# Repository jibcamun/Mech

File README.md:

<h1 align="center">Mech</h1>
<p align="center">A numpad for the elderly</p>

## Purpose
### What is this?
A numpad, consisting numbers from 1 to 9.
### What does this do?
Help people easily access numbers on a keyboard.
### Why does this exists? _(Motivation to build this)_
I have seen old people who use computers only as a calculator and find it hard to type numbers because its stacked at the top and they are more used to the typical calculator layout. _(my grandparents)_

## Features
1. Uses Arduino Pro Micro.
2. Uses MX Switches (1.00u) and Cherry MX Keycaps for a better feel and feedback while pressing a key.  
3. Made it easy to connect and use with a USB connection, thus making it more accessible for the elderly.
4. Simple UX, again making it easily usable for the elderly.
5. All keycaps are angled forward making it easy for "finger typing".

## Schematics

## PCB

## Case

## Zine

## Build Guide
### Step 1
Solder all components to the PCB as indicated by the schematic diagrams.
### Step 2
Take the soldered PCB and place it in an appropriate orientation on the 3D printed component named "Bottom", in accordance with the position of the screw holes.
### Step 3
Place the 3D printed component named "Top" on the assembled setup and press them together _(like a sandwich)_.

## Firmware Flashing
### Step 1
Connect the Pro Micro to your computer using the USB cable.
### Step 2
Install QMK WSYS (if on windows). Enter `qmk flash -kb mech -km default` in the terminal window, to flash the firmware.

## Links 
1. [Bill of Materials (BOM)](https://github.com/jibcamun/Mech/blob/main/Materials/BOM.csv)
2. [PCB Design](https://github.com/jibcamun/Mech/blob/main/PCB%20Design)
3. [3D Case Design](https://cad.onshape.com/documents/927574eef36e39d9a3de9231/w/e5b95da04439b4f215ef18f1/e/b08572cbae5c0041dba6a6c8?renderMode=0&uiState=69ea2cd7de772b1d4ea52e7f)
4. [CAD Export Files](https://github.com/jibcamun/Mech/blob/main/3D%20Models)
5. [3D Export of Design](https://github.com/jibcamun/Mech/blob/main/3D%20Models/mech.step)

## Links for Bill of Materials (Available in BOM)
1. PCBWay: https://www.pcbway.com/
2. ROBU.IN: https://robu.in/product/pro-micro-5v-16m-mini-leonardo-micro-controller-development-board-for-arduino
3. MECKEYS: https://meckeys.com/shop/accessories/keyboard-accessories/key-switches/gateron-mechanical-switch/?attribute_pa_gateron-key-switches=ks-9a10b060nn-x14 
4. Dexterous Manufacturing Labs Pvt Ltd: https://storefront.iamrapid.com/
5. ELECTRONICS COMP: https://www.electronicscomp.com/1n4148-diode

## Attributions 
1. Cherry MX Switches: [row 1 1u blank keycap for cherry mx style switches](https://www.thingiverse.com/thing:5616342) by [LazarosVarvatis](https://www.thingiverse.com/LazarosVarvatis/designs) is licensed under the [Creative Commons - Attribution - Non-Commercial - Share Alike](https://creativecommons.org/licenses/by-nc-sa/4.0/) license. License: [CC BY-NC-SA 4.0](https://creativecommons.org/licenses/by-nc-sa/4.0/)
2. Footprints: [scottokeebs](https://github.com/joe-scotto/scottokeebs)

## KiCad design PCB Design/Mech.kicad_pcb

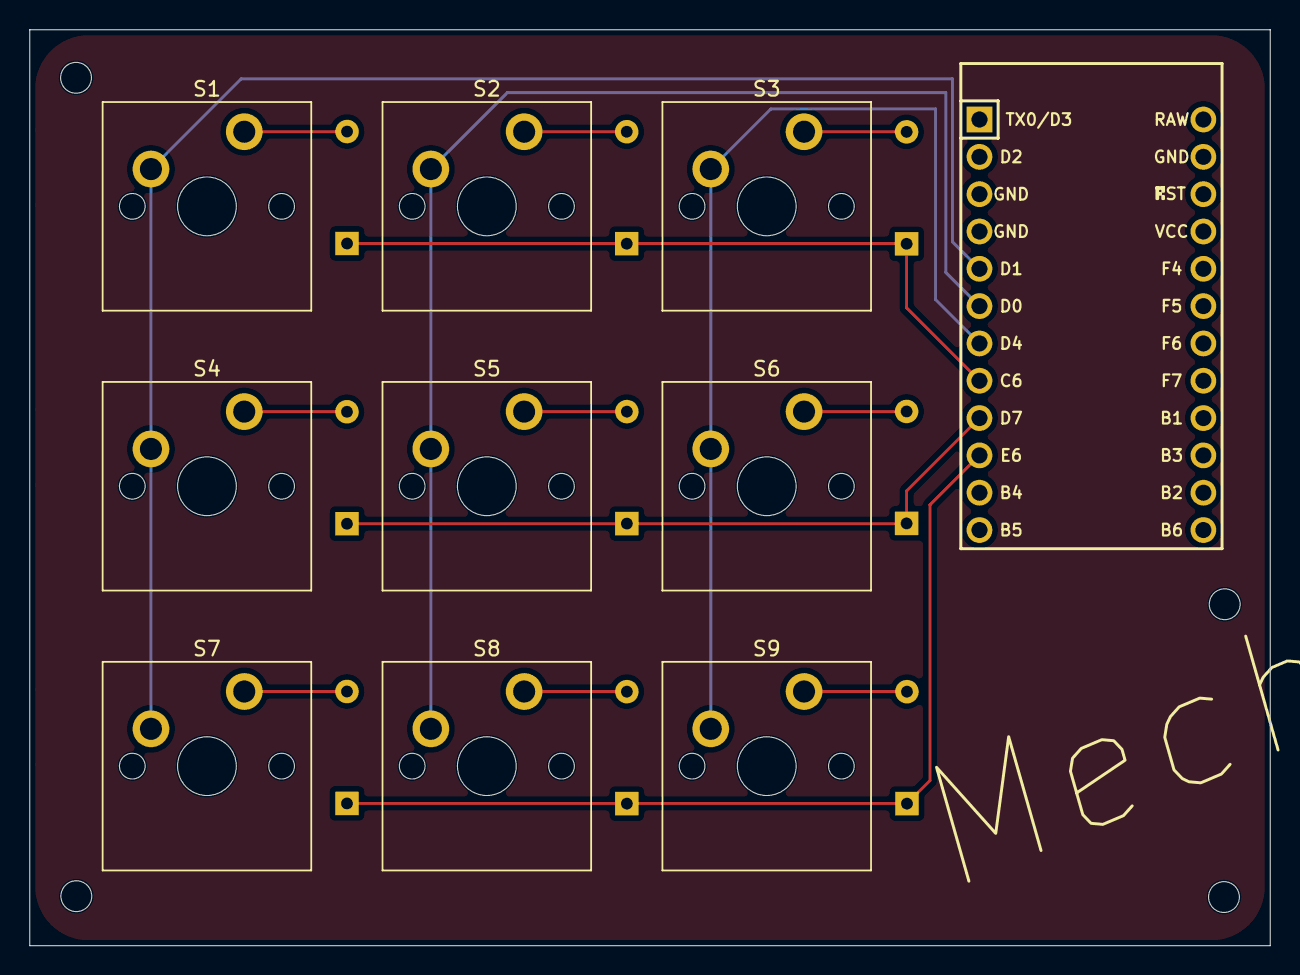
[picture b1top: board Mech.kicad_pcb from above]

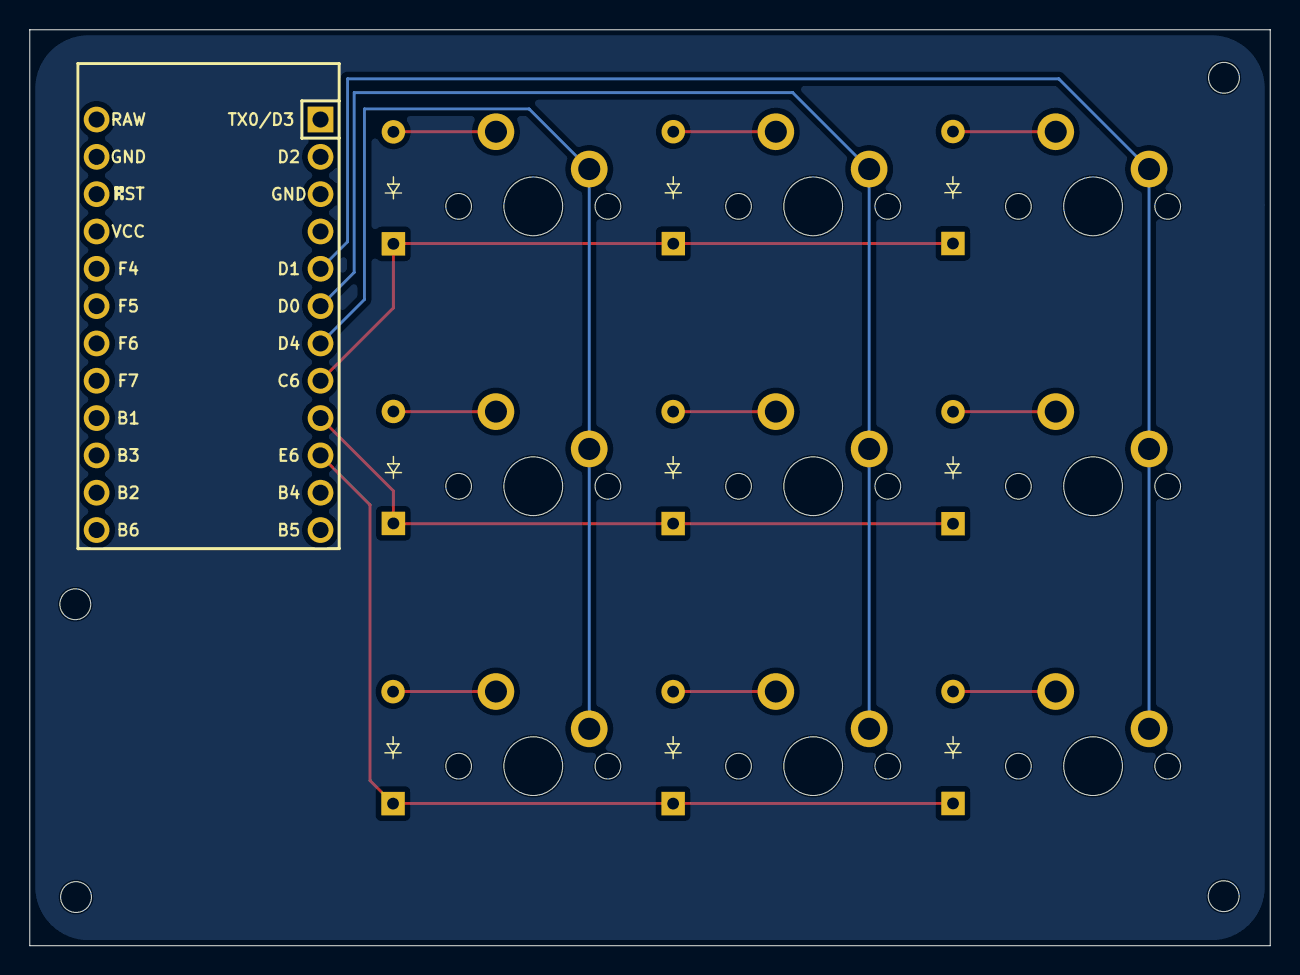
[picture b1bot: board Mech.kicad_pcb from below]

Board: 2 copper layers, 84.4 x 62.3 mm, 19 parts (9 on the bottom side), 15 nets.

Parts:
D1, D2, D3, D4, D5, D6, D7, D8, D9: Diode_DO-35
S1, S2, S3, S4, S5, S6, S7, S8, S9: MX_PCB_1.00u
U1: Arduino_Pro_Micro

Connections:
COL0: S1.1, S4.1, S7.1, U1.7 (4/PD4)
COL1: S2.1, S5.1, S8.1, U1.8 (5/PC6)
COL2: S3.1, S6.1, S9.1, U1.9 (6/PD7)
unnamed: D1.2 (A), S1.2
unnamed: D2.2 (A), S2.2
unnamed: D3.2 (A), S3.2
unnamed: D4.2 (A), S4.2
unnamed: D5.2 (A), S5.2
unnamed: D6.2 (A), S6.2
unnamed: D7.2 (A), S7.2
unnamed: D8.2 (A), S8.2
unnamed: D9.2 (A), S9.2
ROW0: D1.1 (K), D2.1 (K), D3.1 (K), U1.10 (7/PE6)
ROW1: D4.1 (K), D5.1 (K), D6.1 (K), U1.11 (8/PB4)
ROW2: D7.1 (K), D8.1 (K), D9.1 (K), U1.12 (9/PB5)

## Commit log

2026-04-21 Add 3D models
2026-04-21 Modify 3D models
2026-04-21 Add Case Print File
2026-04-21 dummy
2026-04-21 undo dummy
2026-04-22 Add firmware
2026-04-22 Add Images
2026-04-22 Updated firmware
2026-04-22 Add Image
2026-04-23 Add Zine
2026-04-23 Update BOM
2026-04-23 Remove redundant
2026-04-23 structure
2026-04-23 Fix: 3D model
2026-04-23 Fix: Update case
2026-04-23 Add BOM Links
2026-04-23 Add onshape link
2026-04-23 Reorganise files
2026-04-23 Update BOM and README
2026-04-23 Change Arduino Pro Micro Link
2026-04-23 Update README: Add Instructions
2026-04-23 Add SoP
